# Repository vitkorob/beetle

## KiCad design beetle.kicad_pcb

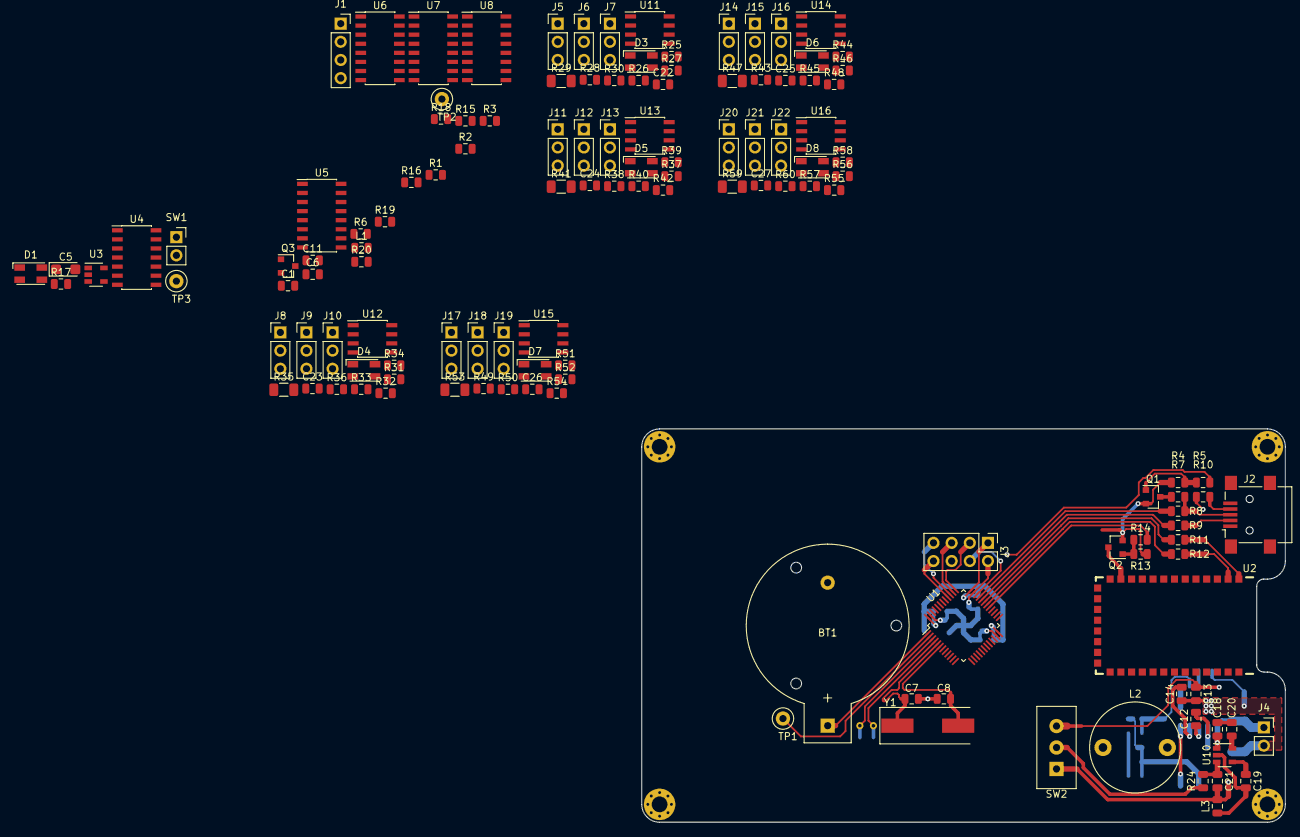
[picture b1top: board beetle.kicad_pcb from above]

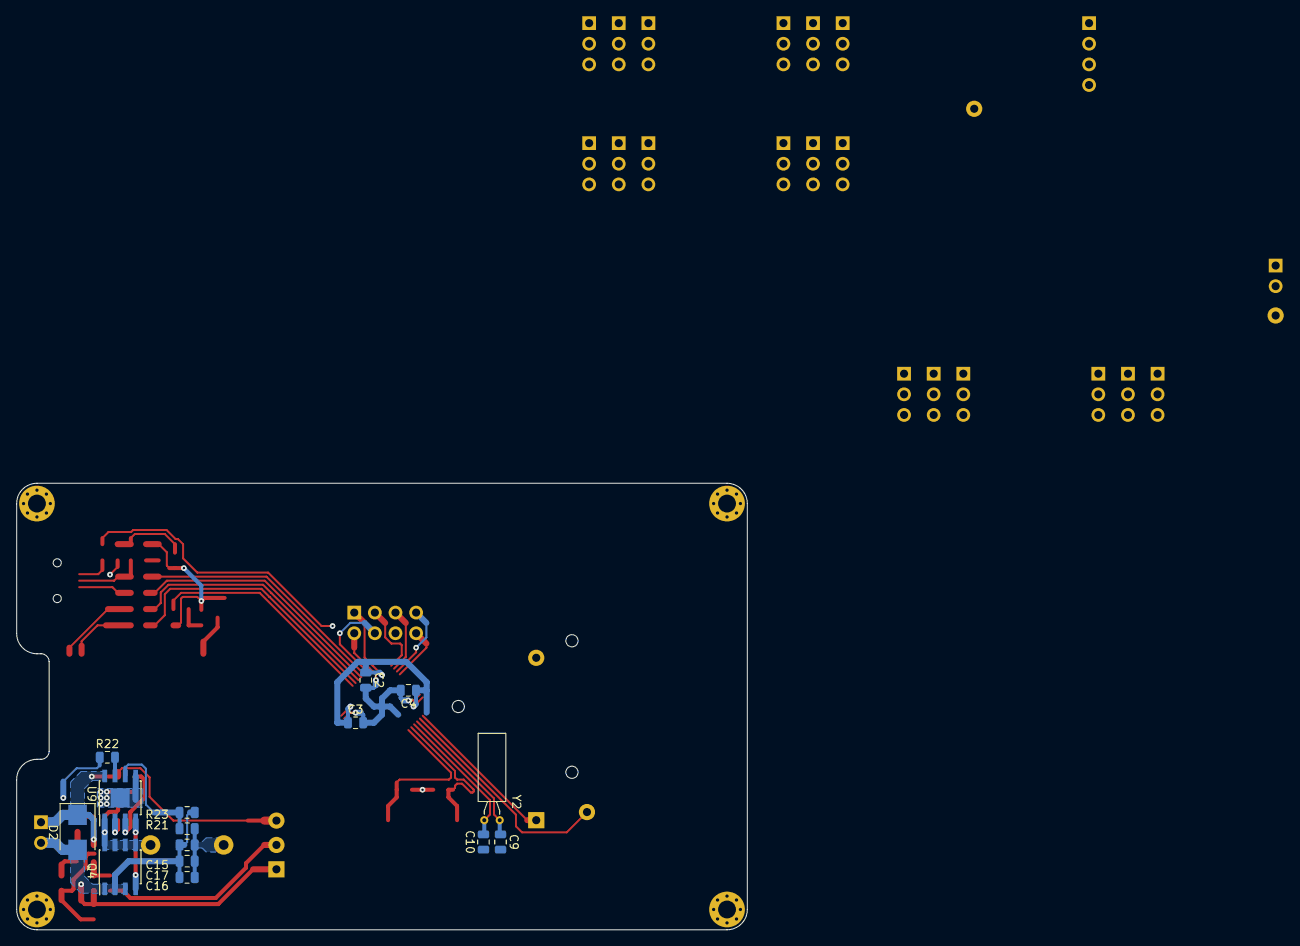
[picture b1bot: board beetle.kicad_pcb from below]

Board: 2 copper layers, 90.0 x 55.0 mm, 148 parts (15 on the bottom side), 118 nets.

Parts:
BT1: 1V8-3V6; CH25-2032LF
C1, C2, C3, C4, C6, C11, C21, C22, C23, C24, C25, C26, C27: 100nF; C_0805_2012Metric
C5: 1uF; CP_EIA-3216-12_Kemet-S
C7, C8: 22pF; C_0805_2012Metric
C9, C10: 10pF; C_0805_2012Metric
C12, C14, C18: 1uF; C_0805_2012Metric
C13, C15, C16, C17: 22uF; C_0805_2012Metric
C19: 10nF; C_0805_2012Metric
C20: 2.2uF; C_0805_2012Metric
D1, D3, D4, D5, D6, D7, D8: LED_Dual_AACC; LED_Wurth_PLCC4_3.2x2.8mm
D2: 9V1; D_SMB
J1: Conn_01x04; PinSocket_1x04_P2.54mm_Vertical
J2: USB_OTG; USB_Mini-B_Lumberg_2486_01_Horizontal
J3: JTAG; PinHeader_2x04_P2.54mm_Vertical
J4: LiPo 2S; PinSocket_1x02_P2.54mm_Vertical
J5, J6, J7, J8, J9, J10, J11, J12, J13, J14, J15, J16, J17, J18, J19, J20, J21, J22: Conn_01x03; PinHeader_1x03_P2.54mm_Vertical
L1, L3: 600R @ 100MHz; L_0805_2012Metric
L2: 3.3uH; L_Radial_D12.5mm_P9.00mm_Fastron_09HCP
Q1, Q2: Q_PNP_BEC; SOT-23
Q3: Q_NPN_BEC; SOT-23
Q4: AO4752; SOIC-8_3.9x4.9mm_P1.27mm
R1, R2, R11, R12, R15, R16, R24, R28, R30, R34, R36, R40, R42, R46, R48, R52, R54, R58, R60: 470; R_0805_2012Metric
R3, R5, R14, R17, R18, R19, R25, R26, R27, R31, R32, R33, R37, R38, R39, R43, R44, R45, R49, R50, R51, R55, R56, R57: 10k; R_0805_2012Metric
R4, R6, R10, R13, R20, R22: 100k; R_0805_2012Metric
R7: 1k5; R_0805_2012Metric
R8, R9: 22; R_0805_2012Metric
R21: 95k3; R_0805_2012Metric
R23: 15k; R_0805_2012Metric
R29, R35, R41, R47, R53, R59: 0.05; R_1206_3216Metric
SW1: SW_Push; PinSocket_1x02_P2.54mm_Vertical
SW2: SW_SPDT; SPDT_P3mm
TP1: TEST; TestPoint_Loop_D2.50mm_Drill1.0mm
TP2: +3V3; TestPoint_Loop_D2.50mm_Drill1.0mm
TP3: GND; TestPoint_Loop_D2.50mm_Drill1.0mm
U1: STM32F103C8Tx; LQFP-48_7x7mm_P0.5mm
U2: HC-06; HC-06_P1.5mm
U3: NC7S08M5; SOT-23-5
U4: 74HC393D; SOIC-14_3.9x8.7mm_P1.27mm
U5, U6, U7, U8: 74HC595D; SOIC-16_3.9x9.9mm_P1.27mm
U9: RT8298; SOIC-8-1EP_3.9x4.9mm_P1.27mm_EP2.35x2.35mm
U10: LP2985-3.3; SOT-23-5
U11, U12, U13, U14, U15, U16: MAX4173FESA+; SOIC-8_3.9x4.9mm_P1.27mm
Y1: 8MHz; Crystal_SMD_HC49-SD
Y2: 32.768kHz; Crystal_C38-LF_D3.0mm_L8.0mm_Horizontal

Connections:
+6V: C15.1, C16.1, C17.1, L2.1, R21.1, R29.1, R35.1, R41.1, R47.1, R53.1, R59.1, U11.8, U12.8, U13.8, U14.8, U15.8, U16.8
+8V: C13.1, C18.1, D2.1, J4.1, SW2.3, U9.8, U10.1
+BATT: BT1.1, U1.1
/BTRX: R12.2, U1.30
/BTTX: R11.2, U1.31
/CLER: Q3.3, R18.2, U4.2
/CURR0: U1.11, U11.4
/CURR1: U1.12, U12.4
/CURR2: U1.13, U13.4
/CURR3: U1.14, U14.4
/CURR4: U1.18, U15.4
/CURR5: U1.19, U16.4
/DISC: R5.2, U1.41
/DM: R9.1, U1.32
/DP: R8.1, U1.33
/ECHO: J1.3, U1.45
/EN: R22.1, U1.26, U9.7
/INIT: D1.2, U1.28
/LED0: D3.1, U5.15
/LED1: D3.2, U5.1
/LED2: D4.1, U6.1
/LED3: D4.2, U6.2
/LED4: D5.1, U6.6
/LED5: D5.2, U6.7
/LED6: D6.1, U7.1
/LED7: D6.2, U7.2
/LED8: D7.1, U7.6
/LED9: D7.2, U7.7
/LED10: D8.1, U8.3
/LED11: D8.2, U8.4
/LEG0: J5.1, R25.1, U5.2
/LEG1: J6.1, R26.1, U5.3
/LEG2: J7.1, R27.1, U5.4
/LEG3: J8.1, R31.1, U5.5
/LEG4: J9.1, R32.1, U5.6
/LEG5: J10.1, R33.1, U5.7
/LEG6: J11.1, R37.1, U6.3
/LEG7: J12.1, R38.1, U6.4
/LEG8: J13.1, R39.1, U6.5
/LEG9: J14.1, R43.1, U7.3
/LEG10: J15.1, R44.1, U7.4
/LEG11: J16.1, R45.1, U7.5
/LEG12: J17.1, R49.1, U8.15
/LEG13: J18.1, R50.1, U8.1
/LEG14: J19.1, R51.1, U8.2
/LEG15: J20.1, R55.1, U8.5
/LEG16: J21.1, R56.1, U8.6
/LEG17: J22.1, R57.1, U8.7
/Leg0/PWR: J5.2, J6.2, J7.2, R29.2, U11.6
/Leg1/PWR: J8.2, J9.2, J10.2, R35.2, U12.6
/Leg2/PWR: J11.2, J12.2, J13.2, R41.2, U13.6
/Leg3/PWR: J14.2, J15.2, J16.2, R47.2, U14.6
/Leg4/PWR: J17.2, J18.2, J19.2, R53.2, U15.6
/Leg5/PWR: J20.2, J21.2, J22.2, R59.2, U16.6
/Power/~OFF: C21.1, R24.1, U10.3
/RCLK: U3.4, U5.12, U6.12, U7.12, U8.12
/SHCL: U1.15, U5.11, U6.11, U7.11, U8.11
/SHDT: U1.17, U5.14
/STCL: U1.22, U3.2, U4.1
/TCK: J3.3, U1.37
/TDI: J3.5, U1.38
/TDO: J3.7, U1.39
/TMS: J3.4, U1.34
/TRIG: J1.2, U6.15
/WKUP: R2.1, U1.10
/~BTON: R14.2, U1.29
/~CLER: R19.2, U1.21, U5.10, U6.10, U7.10, U8.10
/~NRST: C11.1, J3.6, R17.2, U1.7
/~OUEN: R6.2, U1.16, U5.13, U6.13, U7.13, U8.13
/~TRST: J3.8, U1.40
GND: BT1.2, C1.2, C2.2, C3.2, C4.2, C5.2, C6.2, C7.2, C8.2, C9.2, C10.2, C11.2, C18.2, C19.2, C20.2, C22.2, C23.2, C24.2, C25.2, C26.2, C27.2, J1.4, J2.5, J2.6, J3.2, L3.1, Q3.2, R3.2, R10.1, R15.1, R16.1, R20.1, R25.2, R26.2, R27.2, R28.1, R30.1, R31.2, R32.2, R33.2, R34.1, R36.1, R37.2, R38.2, R39.2, R40.1, R42.1, R43.2, R44.2, R45.2, R46.1, R48.1, R49.2, R50.2, R51.2, R52.1, R54.1, R55.2, R56.2, R57.2, R58.1, R60.1, TP3.1, U1.8, U1.23, U1.35, U1.47, U2.13, U2.21, U2.22, U3.3, U4.7, U5.8, U6.8, U7.8, U8.8, U10.2, U11.3, U12.3, U13.3, U14.3, U15.3, U16.3
GNDPWR: C13.2, C14.2, C15.2, C16.2, C17.2, C21.2, D2.2, J4.2, J5.3, J6.3, J7.3, J8.3, J9.3, J10.3, J11.3, J12.3, J13.3, J14.3, J15.3, J16.3, J17.3, J18.3, J19.3, J20.3, J21.3, J22.3, L3.2, Q4.1, Q4.2, Q4.3, R22.2, R23.2, SW2.1, U9.5, U9.9
unnamed: C1.1, R1.1, R2.2
unnamed: C7.1, U1.5, Y1.1
unnamed: C8.1, U1.6, Y1.2
unnamed: C9.1, U1.3, Y2.1
unnamed: C10.1, U1.4, Y2.2
unnamed: C12.1, U9.2
unnamed: C12.2, L2.2, Q4.5, Q4.6, Q4.7, Q4.8, U9.1
unnamed: C14.1, U9.3
unnamed: C19.1, U10.4
unnamed: D1.1, U2.24
unnamed: D1.3, R15.2
unnamed: D1.4, R16.2
unnamed: D3.3, R28.2
unnamed: D3.4, R30.2
unnamed: D4.3, R34.2
unnamed: D4.4, R36.2
unnamed: D5.3, R40.2
unnamed: D5.4, R42.2
unnamed: D6.3, R46.2
unnamed: D6.4, R48.2
unnamed: D7.3, R52.2
unnamed: D7.4, R54.2
unnamed: D8.3, R58.2
unnamed: D8.4, R60.2
unnamed: J2.2, R9.2
unnamed: J2.3, R7.2, R8.2
unnamed: J2.4, R10.2
unnamed: Q1.1, R4.2, R5.1
unnamed: Q1.3, R7.1
unnamed: Q2.1, R13.2, R14.1
unnamed: Q2.3, U2.12
unnamed: Q3.1, R19.1, R20.2
unnamed: Q4.4, U9.4
unnamed: R1.2, SW1.2
unnamed: R3.1, U1.44
unnamed: R11.1, U2.1
unnamed: R12.1, U2.2
unnamed: R21.2, R23.1, U9.6
unnamed: R24.2, SW2.2
unnamed: TP1.1, U1.2
unnamed: U3.1, U4.3
unnamed: U5.9, U6.14
unnamed: U6.9, U7.14
unnamed: U7.9, U8.14
VCC: C2.1, C3.1, C4.1, C20.1, C22.1, C23.1, C24.1, C25.1, C26.1, C27.1, J1.1, J3.1, L1.1, Q1.2, Q2.2, R4.1, R6.1, R13.1, R17.1, R18.1, SW1.1, TP2.1, U1.24, U1.36, U1.48, U3.5, U4.14, U5.16, U6.16, U7.16, U8.16, U10.5, U11.1, U12.1, U13.1, U14.1, U15.1, U16.1
VDDA: C5.1, C6.1, L1.2, U1.9

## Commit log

2018-04-21 Initional commit
2018-04-21 Clarification of footprints
2018-04-22 Four 74HC595 have been added
2018-04-22 SPI to PWM converter is complete
2018-04-30 Adding the new lib
2020-05-12 Sheet with power has been added
